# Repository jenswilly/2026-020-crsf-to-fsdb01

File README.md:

# CRSF to FS-DB01

Firmware that takes RC input from an **ExpressLRS (ELRS) receiver** in **CRSF** format and converts it to the proprietary single-wire protocol of the **FlySky FS-DB01** LED control module. This lets an ELRS radio control the module's lighting functions: turn signals, illumination, reverse/brake, and the no-signal indication.

The FS-DB01 protocol is documented from the reverse-engineered reference implementation in [osos11-Git/F401_FMS_FCX10_LED_REVERSE](https://github.com/osos11-Git/F401_FMS_FCX10_LED_REVERSE), an STM32F401 CubeIDE project. See `Core/Src/main.c` there.

Built on [Zephyr RTOS](https://zephyrproject.org/) 4.4 for the STM32G0B1. The application code is C++23.

## Hardware targets

| Board target    | Hardware                          | MCU                         |
|-----------------|-----------------------------------|-----------------------------|
| `nucleo_g0b1re` | NUCLEO-G0B1RE development board   | STM32G0B1RET6 (LQFP64)      |
| `crsf_fsdb01`   | Custom production board           | STM32G0B1CET6 (LQFP48)      |

Both MCUs have 512 KiB flash and 144 KiB RAM. Both run at 64 MHz from the internal 16 MHz HSI. Neither has a crystal; USB runs from the HSI48 oscillator, trimmed by the CRS against USB SOF.

### Pin assignments

Custom board pins match the schematic, rev. 1 (`pcb/2026-020-crft-to-fsdb01/`).

| Function            | `crsf_fsdb01`        | `nucleo_g0b1re`                      |
|---------------------|----------------------|--------------------------------------|
| CRSF UART (USART1)  | PB7 RX (PB6 TX not connected) | PC4 TX (Arduino D1), PC5 RX (Arduino D0) |
| USB D−/D+           | PA11/PA12            | PA11 (CN10-14)/PA12 (CN10-12)      |
| `led0`              | PB0 (blue, active low) | PA5 (LD4, green)                     |
| `led1`              | PB1 (red-orange, active low) | –                                    |
| `fsdb01` signal out | PA8 (TIM1_CH1)       | PA10 (Arduino D2, TIM1_CH3, placeholder) |
| `vsense0` (ADC1 IN0)| PA0 (Vin)            | PA0 (Arduino A0)                     |
| `vsense1` (ADC1 IN1)| PA1 (VBUS)           | PA1 (Arduino A1)                     |
| SWD                 | PA13 SWDIO, PA14 SWCLK | on-board ST-LINK                   |

The CRSF link runs at 420000 baud, 8N1. The custom board wires only receiver TX → MCU RX (3-pin connector), so there is no telemetry back to the receiver.

The two voltage sense inputs each go through a 100k/33k divider (ratio 33/133 ≈ 0.248), so up to ~13.3 V at the input gives 3.3 V at the pin. Each divider is a `voltage-divider` node in devicetree (`output-ohms`, `full-ohms`), read by Zephyr's voltage-divider sensor driver, which returns the voltage before the divider. The ADC uses 12 bits, the longest sampling time (the divider's source impedance is ~25k) and VDDA as reference, assumed to be 3.3 V (`vref-mv` default).

### Console/CLI

The Zephyr console and shell use **USB CDC ACM** on the MCU's own USB pins on both boards. There is no UART console, except for the optional `nucleo-vcp` build below.

On the Nucleo this needs an **external USB connector**, wired to PA12 (D+), PA11 (D−) and GND on the morpho header. Don't connect its VBUS while the board is also powered from the ST-LINK USB. The ST-LINK virtual COM port (USART2) is not used by default.

For development without the extra connector, the `nucleo-vcp` preset (a debug build) adds `boards/nucleo_vcp_console.overlay`, which moves the console and shell to USART2. Output then appears on the ST-LINK virtual COM port (usually `/dev/ttyACM0`) at 115200 baud. CDC ACM is still built in but isn't the console.

The device currently uses Zephyr's test USB VID/PID (`0x2fe3:0x0004`). Production needs its own.

### Shell commands

`leds` (in `src/shell_leds.cpp`) drives the FS-DB01 driver by hand, for testing the output without a receiver:

| Command                       | Action                                                       |
|-------------------------------|--------------------------------------------------------------|
| `leds status`                 | Output enabled/disabled, auto/manual mode, link state, raw frame (hex), each bit on/off |
| `leds on <led\|all\|0-7>`     | Set bit(s); switches to manual mode                          |
| `leds off <led\|all\|0-7>`    | Clear bit(s); switches to manual mode                        |
| `leds toggle <led\|all\|0-7>` | Toggle bit(s); switches to manual mode                       |
| `leds auto`                   | Back to auto mode: frames follow the CRSF mapping again      |
| `leds enable`                 | Start sending frames                                         |
| `leds disable`                | Stop sending and hold the line low (high with `invert`)      |

LED names (Tab completes them): `right` (bit 0), `left` (1), `ill1` (2), `ill2` (3), `brake` (5), `nosig_fast` (6), `nosig_slow` (7). Use `4` for the unknown bit 4. `all` covers bits 0–7; bit 8 is always 0.

The output is enabled at boot. In auto mode (the default), the control thread sets the frame from CRSF every 10 ms, so on/off/toggle switch to manual mode first, or their changes would be overwritten straight away. Manual mode lasts until `leds auto` or a reboot. enable/disable work in either mode; on/off/toggle only change the frame bits.

`voltage` (in `src/shell_voltage.cpp`) reads both voltage sense inputs and prints the input voltage (before the divider) and the voltage at the pin:

```
> voltage
vsense0  12.012 V   (pin 2.980 V)
vsense1   0.004 V   (pin 0.000 V)
```

`crsf` (in `src/shell_crsf.cpp`) shows what is arriving on the CRSF input:

| Command         | Action                                                                     |
|-----------------|----------------------------------------------------------------------------|
| `crsf status`   | Age of the latest RC and link frames, byte/frame/error counters, link statistics |
| `crsf channels` | The 16 channels from the latest RC frame, raw and in µs                    |

If `Bytes` goes up but there are no frames, check the baud rate and that the signal isn't inverted. CRC errors point to noise or a bad connection.

`dfu` (in `src/shell_dfu.cpp`) reboots into the USB DFU bootloader; see below.

### Firmware update over USB (DFU)

The `dfu` shell command reboots into the STM32's built-in system bootloader, which enumerates on USB as `0483:df11`. No BOOT0 pin or jumper is used; the option bytes stay at their factory defaults. Then flash with:

```sh
dfu-util -d 0483:df11 -a 0 -s 0x08000000:leave -D build/custom/zephyr/zephyr.bin
```

or use the wrapper, which checks the file and that the bootloader is present first:

```sh
scripts/dfu_flash.sh build/custom/zephyr/zephyr.bin
```

`-d 0483:df11` selects the STM32 bootloader, so other DFU-capable devices, such as some laptop webcams, are never targeted. If several boards are in DFU mode at once, add `-S <serial>` (shown by `dfu-util -l`), or set `DFU_SERIAL=<serial>` for the script (with sudo: `sudo DFU_SERIAL=… scripts/dfu_flash.sh …`). **After flashing, power-cycle the board fully.** While erasing, the bootloader sets the `EMPTY` flag in `FLASH_ACR`. While it's set, every reset starts the bootloader again instead of the new firmware, and only a real power-on clears it. `:leave` and the reset button don't, so the board stays in DFU mode. On the Nucleo, the ST-LINK USB also powers the board, so unplug that cable too. Without a power cycle, clear the flag over SWD instead:

```sh
openocd -f <board openocd.cfg> -c "init; halt; mmw 0x40022000 0 0x00010000; reset run; shutdown"
```

How it works (`src/bootloader.cpp`): the command stores a marker in `.noinit` RAM and reboots. Early in the next boot, before the clock driver runs, the marker is found and the firmware jumps to system memory (`0x1FFF0000`), so the bootloader starts from an almost-reset state.

This only works while the firmware is running. To recover a board whose firmware doesn't boot, use SWD.

The host needs permission to open `0483:df11`, e.g. a udev rule like the one for the ST-LINK:
`SUBSYSTEM=="usb", ATTR{idVendor}=="0483", ATTR{idProduct}=="df11", MODE="0660", GROUP="plugdev"`.

## Protocols

### Input: CRSF from an ELRS receiver

- UART, **420000 baud, 8N1**, non-inverted, full duplex: receiver TX → MCU RX. MCU TX → receiver RX is only needed for telemetry.
- Frame layout: `[sync 0xC8] [len] [type] [payload …] [CRC8]`. `len` counts type + payload + CRC. The CRC8 uses the DVB-S2 polynomial `0xD5` and covers type + payload.
- `0x16` *RC channels packed*: 16 channels × 11 bits, little-endian bit-packed. Nominal values run 172–1811 (≈ 988–2012 µs), with 992 at center.
- `0x14` *Link statistics*: RSSI, LQ, SNR, etc. Useful for failsafe/no-signal detection.
- The firmware parses frames in the UART RX interrupt (`src/crsf.cpp`) and keeps only the latest channels and link statistics, with the time each arrived. The protocol code (`src/crsf_parser.cpp`) has no Zephyr dependencies. It drops a partial frame after 1750 µs, as Betaflight does, and then resyncs on the next `0xC8`. Other frame types are counted and ignored.

### Output: FS-DB01 LED module

All of the following comes from the reverse-engineered reference implementation; it isn't an official specification.

- A single line, idle **low**. The reference drives it from a 1 ms time base; this firmware generates it with TIM1 in PWM mode (one 3 ms timer period per bit, compare value = high time), so the edges don't depend on interrupt latency. TIM1 is reserved for the driver on both boards.
  If the signal goes through an inverting level shifter, add the `invert` property to the `fsdb01` devicetree node. The driver then inverts every level it drives, including the disabled state.
- A frame is **9 bits**, sent bit 0 first, followed by **3 ms low**. Each bit takes 3 ms, so a frame takes 30 ms and repeats continuously.
  - `1` = 2 ms high, then 1 ms low
  - `0` = 1 ms high, then 2 ms low

| Bit | Function                                         |
|-----|--------------------------------------------------|
| 0   | Left turn signal (flashing)                      |
| 1   | Right turn signal (flashing)                     |
| 2   | Not connected                                    |
| 3   | Front and top lights                             |
| 4   | Brake                                            |
| 5   | Not connected                                    |
| 6   | No-signal fast blink (lower prio. than 7)        |
| 7   | No-signal slow blink (higher prio. than 6)       |
| 8   | Always 0                                         |

The reference firmware's power-on state is bits 6 and 7 set: the no-signal indication.

### Mapping and failsafe

A control thread (`src/control.cpp`) checks the latest CRSF channels every 10 ms and sets the FS-DB01 frame. Each rule (`src/mapping.cpp`) turns an output on while one channel is inside an inclusive interval in µs. An output is on if any of its rules match. For now the rules are hardcoded. Later they'll be configurable from the shell and stored in flash.

| Output         | Channel | Interval (µs) | Meaning               |
|----------------|---------|---------------|-----------------------|
| Right (bit 0)  | 5       | 1700–2100     | ch5 high              |
| Left (bit 1)   | 5       | 900–1300      | ch5 low               |
| Ill. 1 (bit 2) | 6       | 1300–2100     | ch6 mid or high       |
| Ill. 2 (bit 3) | 6       | 1700–2100     | ch6 high              |
| Brake (bit 5)  | 2       | 900–1450      | throttle below center |

**Failsafe:** the output is enabled at boot with the failsafe frame, bit 6 only (no-signal, fast blink). It switches to the mapped frame once RC channel frames arrive, and back to the failsafe frame if none arrive for 500 ms. ELRS receivers stop sending RC frames when the link is lost.

RC Channels are mapped with 988 us being mimimum, 1500 being middle and 2012 being maximum value.

## Development environment

Everything is built in a VS Code devcontainer (`.devcontainer/`), based on Ubuntu 24.04:

- Zephyr **v4.4.2** west workspace in `/opt/zephyrproject` (`ZEPHYR_BASE` is set). Only the `cmsis`, `cmsis_6` and `hal_stm32` modules are fetched.
- Zephyr SDK **1.0.1** in `/opt/zephyr-sdk-1.0.1` (ARM GCC 14.3 + host tools)
- Python venv with west in `/opt/zephyr-venv` (on `PATH`)
- CMake **4.4.3** and Ninja **1.13.2** from the official release binaries (Ubuntu's packages are too old)
- OpenOCD, stlink-tools, gdb-multiarch

Open the folder in VS Code and choose **Dev Containers: Reopen in Container**. The first image build downloads Zephyr and the SDK and takes a while.

The container runs privileged with the host's `/dev` bind-mounted, so ST-LINK probes and `/dev/ttyACM*` ports work, including ones that re-enumerate after a board reset. The **host** needs udev rules for the ST-LINK. Your user must be in the `dialout` and `plugdev` groups.

To change tool versions, edit `ZEPHYR_VERSION`, `CMAKE_VERSION` or `NINJA_VERSION` in `devcontainer.json`, then rebuild the container.

## Building, flashing and debugging

Builds are driven by **CMake presets** (`CMakePresets.json`), one per board and build mode:

| Preset         | Board target                | Mode    | Build directory        |
|----------------|-----------------------------|---------|------------------------|
| `nucleo`       | `nucleo_g0b1re/stm32g0b1xx` | release | `build/nucleo/`        |
| `nucleo-debug` | `nucleo_g0b1re/stm32g0b1xx` | debug   | `build/nucleo-debug/`  |
| `nucleo-vcp`   | `nucleo_g0b1re/stm32g0b1xx`, console on ST-LINK VCP | debug | `build/nucleo-vcp/` |
| `custom`       | `crsf_fsdb01/stm32g0b1xx`   | release | `build/custom/`        |
| `custom-debug` | `crsf_fsdb01/stm32g0b1xx`   | debug   | `build/custom-debug/`  |

The build mode is the `APP_BUILD_MODE` cache variable, set by the hidden `debug`/`release` presets. `CMakeLists.txt` adds `debug.conf` or `release.conf` on top of `prj.conf` for every board, so mode-specific Kconfig goes there; `debug.conf` builds with `-O0` (`CONFIG_NO_OPTIMIZATIONS`), thread info, an MPU stack guard and extra shell commands. `-O0` rather than `-Og` because the Cortex-M0+ has only 4 hardware breakpoints, and at `-Og` one source line often compiles to several copies that each need one (OpenOCD: `Can not find free FPB Comparator`). A preset can still add board-specific fragments with `EXTRA_CONF_FILE`; they're merged after the mode file.

To add a board: a hidden `<board>-board` preset with `BOARD`, plus `<board>` (inherits `release`) and `<board>-debug` (inherits `debug`) presets, and the matching build presets, tasks and launch configs.

### In VS Code

- **Build:** choose the preset in the CMake Tools status bar, then click Build (F7). IntelliSense follows the active preset.
- **Flash/menuconfig:** use the tasks in `.vscode/tasks.json` (*Tasks: Run Task* → `Flash: nucleo`, `Flash: nucleo-debug`, `Flash: custom`, …).
- **Debug:** use the Cortex-Debug launch configs in `.vscode/launch.json` (`Debug: nucleo-debug`, `Debug: nucleo-vcp`, `Debug: custom-debug`, `Attach: custom-debug`). They use the debug builds, build first, then flash and debug via OpenOCD + ST-LINK.

### From the command line

Run these inside the container, from the project root:

```sh
cmake --preset custom                             # configure
cmake --build --preset custom                     # build
cmake --build --preset custom --target flash      # flash (OpenOCD + ST-LINK)
cmake --build --preset custom --target menuconfig # Kconfig
cmake --build --preset custom --target ram_report # memory usage
```

Replace `custom` with another preset, e.g. `custom-debug` or `nucleo`. For a clean rebuild, delete the build directory, or run `cmake --preset <name> --fresh`.

The `flash`, `debug` and `debugserver` targets call Zephyr's west runners internally. `west` still works on the same build directories, e.g. `west flash -d build/custom`, or `west flash -d build/custom -r <runner>` to pick another runner. Both boards also define STM32CubeProgrammer, pyOCD and J-Link runners, but only OpenOCD is installed in the container. The stock Nucleo board defaults to STM32CubeProgrammer, so the `nucleo` presets set `BOARD_FLASH_RUNNER=openocd`. Flashing and Cortex-Debug both use the OpenOCD and GDB from the Zephyr SDK.

## Project layout

```
CMakeLists.txt                  App build; adds this repo as a BOARD_ROOT
NOTES.md                        Handoff notes: status, decisions, open items
CMakePresets.json               Configure/build presets per board and mode
debug.conf, release.conf        Kconfig per build mode, added on top of prj.conf
prj.conf                        Common Kconfig: C++23, full libstdc++, logging, shell, USB CDC ACM
Kconfig                         App Kconfig root: sources drivers/Kconfig, then Zephyr
src/                            Application sources (C++); shell commands in src/shell_*.cpp
  bootloader.cpp                Reboot into the STM32 USB DFU bootloader (`dfu` command)
  crsf.cpp                      CRSF receiver: UART ISR, latest channels/link statistics
  crsf_parser.cpp               CRSF frame parser, CRC, channel decoding (no Zephyr dependencies)
  mapping.cpp                   CRSF channel → FS-DB01 frame rules
  control.cpp                   Control thread: mapping and failsafe
drivers/                        In-tree device drivers (C)
  fsdb01/                       FS-DB01 driver: source, header, Kconfig
dts/bindings/                   Devicetree bindings for the in-tree drivers (flysky,fsdb01)
boards/
  usb_console.dtsi              CDC ACM console/shell node, shared by both boards
  nucleo_g0b1re.overlay         Nucleo: crsf-uart alias, USB console, frees PA11/PA12
  nucleo_vcp_console.overlay    Nucleo dev option (nucleo-vcp preset): console on ST-LINK VCP
  crsf_fsdb01.overlay           Custom board: USB console
  custom/crsf_fsdb01/           Custom board definition (Zephyr hardware model v2)
scripts/dfu_flash.sh            Flash a .bin over USB DFU (STM32 system bootloader)
.vscode/                        Tasks (build/flash/menuconfig) and Cortex-Debug launch configs
.devcontainer/                  Dockerfile + devcontainer.json
```

The application uses devicetree **aliases** (`crsf-uart`, `led0`, …) instead of board-specific code. Each board, or its overlay, maps the aliases to its hardware.

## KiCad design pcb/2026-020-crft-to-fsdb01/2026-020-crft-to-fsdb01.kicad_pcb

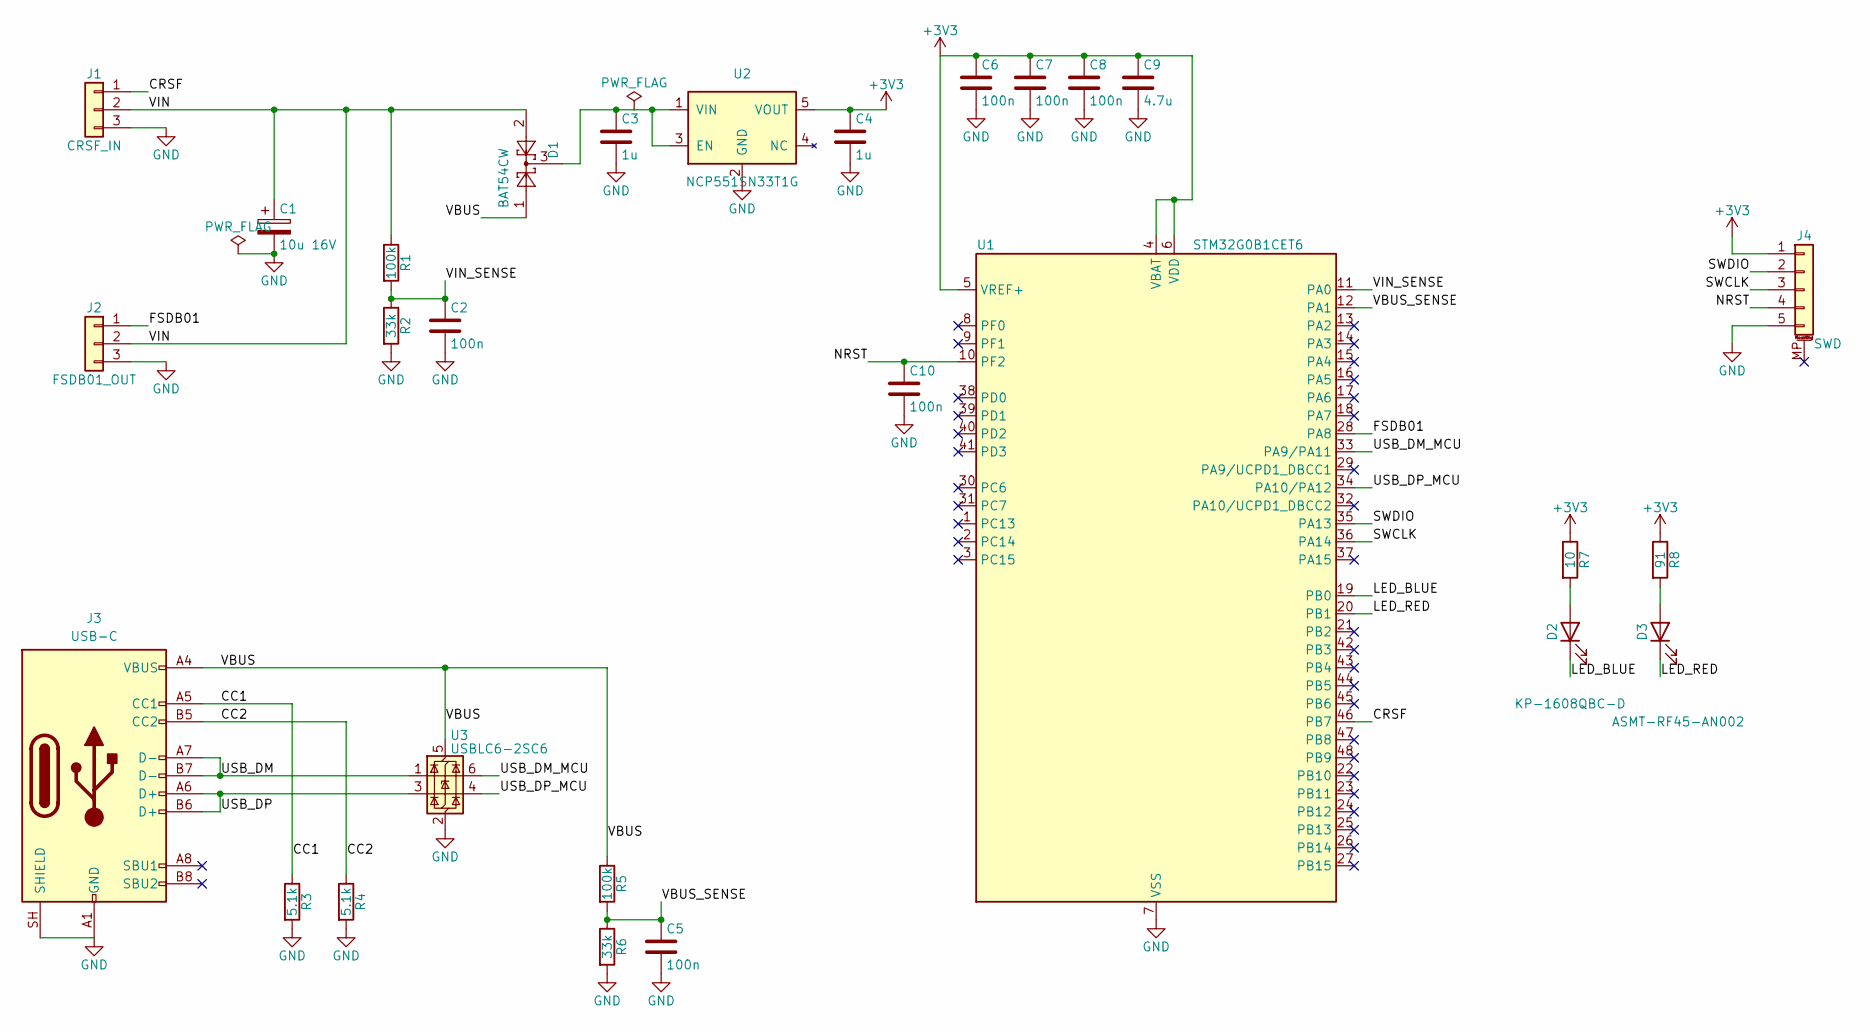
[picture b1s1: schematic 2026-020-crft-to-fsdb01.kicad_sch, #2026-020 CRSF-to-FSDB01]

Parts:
C1: 10u 16V; CP_EIA-3528-21_Kemet-B; MPN TAJB106M016RNJ
C2, C5, C6, C7, C8, C10: 100n; C_0603_1608Metric
C3, C4: 1u; C_0603_1608Metric
C9: 4.7u; C_0603_1608Metric
D1: BAT54CW; SOT-323_SC-70; MPN BAT54CW
D2: KP-1608QBC-D; LED_0603_1608Metric
D3: ASMT-RF45-AN002; LED_0603_1608Metric
J1: CRSF_IN; PinHeader_1x03_P2.54mm_Vertical
J2: FSDB01_OUT; PinHeader_1x03_P2.54mm_Vertical
J3: USB-C; USB_C_Receptacle_GCT_USB4105-xx-A_16P_TopMnt_Horizontal; MPN USB4105-GF-A-120
J4: SWD; Molex_PicoBlade_53261-0571_1x05-1MP_P1.25mm_Horizontal
R1, R5: 100k; R_0603_1608Metric; Tolerance 1%
R2, R6: 33k; R_0603_1608Metric; Tolerance 1%
R3, R4: 5.1k; R_0603_1608Metric
R7: 10; R_0603_1608Metric
R8: 91; R_0603_1608Metric
U1: STM32G0B1CET6; LQFP-48_7x7mm_P0.5mm
U2: NCP551SN33T1G; SOT-23-5
U3: USBLC6-2SC6; SOT-23-6

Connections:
+3V3: C4.1, C6.1, C7.1, C8.1, C9.1, J4.1, R7.1, R8.1, U1.4 (VBAT), U1.5 (VREF+), U1.6 (VDD), U2.5 (VOUT)
/CC1: J3.A5 (CC1), R3.1
/CC2: J3.B5 (CC2), R4.1
/CRSF: J1.1, U1.46 (PB7)
/FSDB01: J2.1, U1.28 (PA8)
/LED_BLUE: D2.1 (K), U1.19 (PB0)
/LED_RED: D3.1 (K), U1.20 (PB1)
/NRST: C10.1, J4.4, U1.10 (PF2)
/SWCLK: J4.3, U1.36 (PA14)
/SWDIO: J4.2, U1.35 (PA13)
/USB_DM: J3.A7 (D-), J3.B7 (D-), U3.1 (I/O1)
/USB_DM_MCU: U1.33 (PA9/PA11), U3.6 (I/O1)
/USB_DP: J3.A6 (D+), J3.B6 (D+), U3.3 (I/O2)
/USB_DP_MCU: U1.34 (PA10/PA12), U3.4 (I/O2)
/VBUS: D1.1, J3.A4 (VBUS), J3.A9 (VBUS), J3.B4 (VBUS), J3.B9 (VBUS), R5.1, U3.5 (VBUS)
/VBUS_SENSE: C5.1, R5.2, R6.1, U1.12 (PA1)
/VIN: C1.1, D1.2, J1.2, J2.2, R1.1
/VIN_SENSE: C2.1, R1.2, R2.1, U1.11 (PA0)
GND: C1.2, C2.2, C3.2, C4.2, C5.2, C6.2, C7.2, C8.2, C9.2, C10.2, J1.3, J2.3, J3.A1 (GND), J3.A12 (GND), J3.B1 (GND), J3.B12 (GND), J3.SH (SHIELD), J4.5, R2.2, R3.2, R4.2, R6.2, U1.7 (VSS), U2.2 (GND), U3.2 (GND)
unnamed: D2.2 (A), R7.2
unnamed: D3.2 (A), R8.2
unnamed: C3.1, D1.3, U2.1 (VIN), U2.3 (EN)

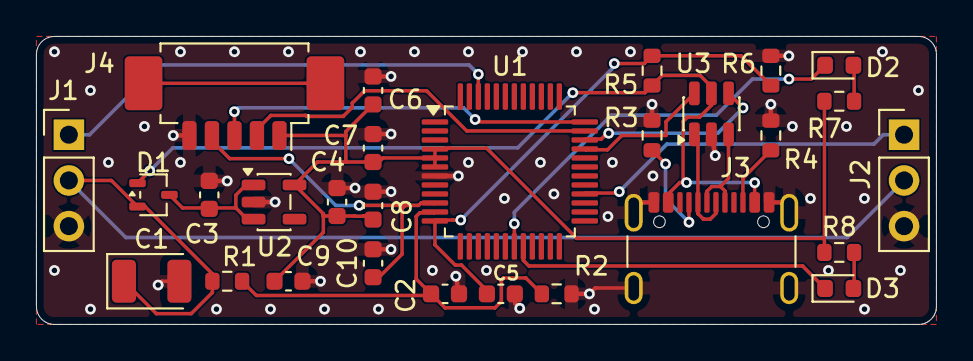
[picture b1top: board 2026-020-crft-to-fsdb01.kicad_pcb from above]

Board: 2 copper layers, 50.0 x 16.0 mm, 28 parts (0 on the bottom side), 22 nets.

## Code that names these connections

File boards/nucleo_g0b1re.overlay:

/*
 * NUCLEO-G0B1RE
 *
 * Console/shell on USB CDC ACM via an external USB connector wired to
 * PA12 = D+ (CN10-12), PA11 = D- (CN10-14) and GND.
 * CRSF link on USART1: PC4 = TX (Arduino D1), PC5 = RX (Arduino D0).
 * FS-DB01 signal out: PA10 (Arduino D2, TIM1_CH3), placeholder.
 * Voltage sense inputs: PA0 (Arduino A0) and PA1 (Arduino A1) on ADC1.
 *
 * SPDX-License-Identifier: Apache-2.0
 */

#include <zephyr/dt-bindings/adc/adc.h>

#include "usb_console.dtsi"

/ {
	/* TODO: placeholder pin, FS-DB01 output not assigned yet */
	fsdb01: fsdb01 {
		compatible = "flysky,fsdb01";
		timer = <&timers1>;
		channel = <3>;
		pinctrl-0 = <&tim1_ch3_pa10>;
		pinctrl-names = "default";
	};

	/* Input voltage dividers: 100k over 33k, ratio 33/133 = 0.248 */
	vsense0: vsense0 {
		compatible = "voltage-divider";
		io-channels = <&adc1 0>;
		output-ohms = <33000>;
		full-ohms = <(100000 + 33000)>;
	};

	vsense1: vsense1 {
		compatible = "voltage-divider";
		io-channels = <&adc1 1>;
		output-ohms = <33000>;
		full-ohms = <(100000 + 33000)>;
	};

	aliases {
		crsf-uart = &usart1;
		fsdb01 = &fsdb01;
		vsense0 = &vsense0;
		vsense1 = &vsense1;
	};
};

&usart1 {
	current-speed = <420000>;
	/* RX FIFO: without it, ISR latency over ~24 us (one byte) overruns */
	fifo-enable;
};

/* Used directly by the FS-DB01 driver; its pwm and counter children stay disabled */
&timers1 {
	status = "okay";
};

/* PA0/PA1 pinctrl, clock and status come from the stock board */
&adc1 {
	#address-cells = <1>;
	#size-cells = <0>;

	/* Max sampling time (160.5 cycles, 10 us): the dividers' source impedance is ~25k */
	channel@0 {
		reg = <0>;
		zephyr,gain = "ADC_GAIN_1";
		zephyr,reference = "ADC_REF_INTERNAL";
		zephyr,acquisition-time = <ADC_ACQ_TIME_MAX>;
		zephyr,resolution = <12>;
	};

	channel@1 {
		reg = <1>;
		zephyr,gain = "ADC_GAIN_1";
		zephyr,reference = "ADC_REF_INTERNAL";
		zephyr,acquisition-time = <ADC_ACQ_TIME_MAX>;
		zephyr,resolution = <12>;
	};
};

/* PA11/PA12 are used by USB; release them from I2C2 and FDCAN1 */
&i2c2 {
	status = "disabled";
};

&fdcan1 {
	status = "disabled";
};
